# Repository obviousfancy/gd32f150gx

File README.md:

# gd32f150gx

## Overview

The project, named "gd32f150gx," is a development effort focused on creating a microcontroller-based system using the GD32F150Gx series microcontrollers with a QFN28 package. The primary objectives include real-time processing capabilities and hardware design optimization for low noise.

## Project Description

- **Description**: A test board based on GD32F150Gx microcontroller with QFN28 packaging.
- **Features**:
  - 2-layer PCB design.
  - SWD via QWIIC Connector

## Technologies and Tools

- **Hardware**: GD32, QWIIC Connector
- **Software/Hardware Design Tools**: KiCad

## Repository Structure

- `/src`: Firmware developed in C (not present in the provided structure).
- `/hardware`: Schematic and PCB design files.
  - `00_gd32f150/`: Subdirectory for specific hardware design versions.
    - KiCad project files (`.kicad_sch`, `.kicad_pcb`, etc.): Schematic and PCB layout files.
- `/assets`: Images and block diagrams.
  - `00_gd32f150.pdf`, `00_gd32f150.svg`, `gd32f150.png`
- `/docs`: General project documentation.(not present in the provided structure)

## Gallery

### Prototypes
- **Physical Prototype**: 
- **PCB Design**: 

## Installation and Usage

1. Clone the repository: `git clone [url-del-repo]`
2. Open the project in KiCad.

## License

The project is licensed under the MIT License. For more details, refer to the `LICENSE` file.

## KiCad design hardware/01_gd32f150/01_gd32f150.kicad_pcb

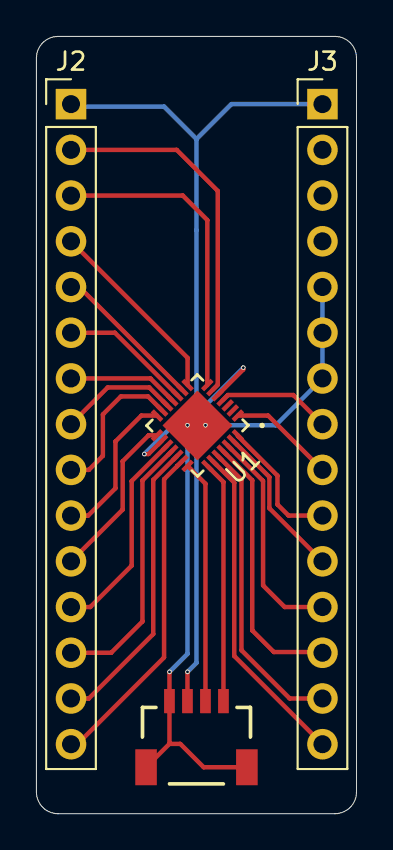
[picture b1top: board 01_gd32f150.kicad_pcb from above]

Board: 2 copper layers, 17.8 x 43.2 mm, 4 parts (0 on the bottom side), 26 nets.

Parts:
J2: LeftConn; PinHeader_1x15_P2.54mm_Vertical
J3: RightConn; PinHeader_1x15_P2.54mm_Vertical
J4: Qwiic_RA; JST_1x04_P1.0mm_Horizontal_SMD
U1: GD32F150GxUx; QFN28_4X4X0.8

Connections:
+3.3V: J2.1, J3.1, J4.2, U1.5 (VDDA), U1.16 (VDD)
A0: J2.2, U1.6 (PA0)
A1: J2.3, U1.7 (PA1)
A2: J2.4, U1.8 (PA2)
A3: J2.5, U1.9 (PA3)
A4: J2.6, U1.10 (PA4)
A5: J2.7, U1.11 (PA5)
A6: J2.8, U1.12 (PA6)
A7: J2.9, U1.13 (PA7)
BOOT: J3.9, U1.1 (BOOT0)
GND: J3.5, J3.6, J3.7, J4.1, J4.NC1 (NC), J4.NC2 (NC), U1.0 (EPAD)
NRST: J3.8, U1.4 (NRST)
PA9: J2.12, U1.17 (PA9)
PA10: J2.13, U1.18 (PA10)
PA11: J2.14, U1.19 (PA11)
PA12: J2.15, U1.20 (PA12)
PA15: J3.15, U1.23 (PA15)
PB0: J2.10, U1.14 (PB0)
PB1: J2.11, U1.15 (PB1)
PB3: J3.14, U1.24 (PB3)
PB4: J3.13, U1.25 (PB4)
PB5: J3.12, U1.26 (PB5)
PB6: J3.11, U1.27 (PB6)
PB7: J3.10, U1.28 (PB7)
SWCLK: J4.4, U1.22 (PA14)
SWDIO: J4.3, U1.21 (PA13)

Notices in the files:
README.md:
License: MIT
